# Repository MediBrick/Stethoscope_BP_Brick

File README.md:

# Stethoscope with Pressure Sensor

The stethoscope and blood pressure brick consists of a sound as well as pressure recorder. For sound the I2S (Inter-Integrated Circuit Sound) bus is used to communicate with the microcontroller. This interface allows streaming and recording audio to an audio codec board. The Everest Semiconductor [ES8388 audio codec](datasheets/ES8388%20DS.pdf) was chosen because its supported by Arduino Audio Tools library and Arduino Audio Driver and because Espressif created the Lyrat Audio modules with published reference [designs](datasheets/esp32-lyrat-v4-schematic.pdf).

Sound was recorded with pui audio analog MEMS microphones [AMM-2742](datasheets/Microphone-AMM-2742-T-R.pdf) that are mounted on the printed circuit board.

However a new design is developed to use electret microphones that are attached to the flexible stethoscope tubing.

Two microphones are used where one is connected to the stethoscope and the other recording the background. An [dual differential amplifier](datasheets/opa344.pdf) is used to low pass filter and amplify the signal from the microphone, however amplification would not be needed for the ES8388 codec. Pressure is measured with a Honeywell MPR pressure sensor [MPRLS0300YG](datasheets/MPR_Pressure_HWSC_S_A0016036563_1-3073392.pdf) that convers the physiological range of 0 to 200 mm Hg.

## Costs &#36;

| Item        | Quantity at Purchase | Costs  | Source            | Cost per Brick
|---                          | ---  | ---    | ---               | ---
| Microcontroller             |  1   | $17.5  | [Adafruit](https://www.adafruit.com/product/5477)          | $17.5
| Display                     |  5   | $13    | [Amazon](https://a.co/d/1QH0Ab9)            | $3
| Button                      | 25   | $9     | [Amazon](https://a.co/d/8KAuTwC) | $0.5 
| Battery                     |  1   | $10     | [Adafruit](https://www.adafruit.com/product/258)        | $10
| PCB                         |  5   | $45.18 | PCBWay            | $9
| Parts and Assembly          |  2   | $56.55 | PCBWay            | $29
| MPRLS0300YG (pressure)      |  2   | $35    | [DigiKey](https://www.digikey.com/en/products/detail/honeywell-sensing-and-productivity-solutions/MPRLS0300YG00001B/10231660) | $17.5
| PUI AOM-5024L-HD-R (microphone)  |  2  | $4.2 | [Mouser](https://mou.sr/43AdqZY) | $8.4
| 3.5mm Audio jack stereo out(*)   | 1 | $0.9 | [Mouser](https://mou.sr/4uOWvy2) | $0.9
| 3.5mm Audio jacl mic in & stereo out(*) | 1 | $1.2 | [Mouser](https://mou.sr/4fyV8PS) | $1.2 |
| Stethoscope                 |  1   | $25    | [Amazon](https://a.co/d/7tQgoKs) | $25
| Arm Cuff                    |  1   | $17    | [Amazon](https://a.co/d/gKueGYV) | $17
| Assorted Wires              |8m    | $15    | [Amazon](https://a.co/d/58djefc) | $1
| Assorted Screws and Nuts    |100   |  $7    | Amazon            | $0.05
| Silocone Tubing             |  1   |  $9    | [Amazon](https://a.co/d/5GLJtFr) | $2
| Luer Lock female 3/32 barb  | 10   |  $9    | [Amazon](https://a.co/d/hxruOyw) | $1
| Luer Lock male 5/32 barb    | 10   |  $8    | [Amazon](https://a.co/d/c4cmtBQ) | $1
| Stainless Steel Tubing      |250mm | $10    | Amazon            | $2 |
| Assorted 3D printed parts   |      |        |                   | $3
|  **(*)** if not available at manufacturer, DIY |
| **Total with blood pressure**     |      |        |                   | **$140**
| **Total without blood pressure**  |      |        |                   | **$100**

Electronic components, excluding the pressure sensor, are $14 per board.

The pressure sensor was mounted in-house as the PCB assembly service did not have access to an inexpensive source.

## Software &#128187;

Main Program in Arduino folder:

- MediBrick_Stethoscope_BP_Microcontroller_Software: Refer to [Microcontroller_Software.md](Microcontroller_Software.md) for installation and usage instructions.

Test software is located in Arduino folder.

- MediBrick_Stethoscope_ES8388_to_CSV:
Prints the two-channel audio signal to the serial port for visualization with SerialUI application.

- MediBrick_Stethoscope_ES8388_TestSound: Creates test tone in left and right channels for headphones.

- MediBrick_Stethoscope_ES8388_to_Headphone: Plays the recorded sound to the headphone.

- MediBrick_Stethoscope_PressureTest: Test the arm cuff pressure sensor.

## Electronics Design &#128268;

The following files are needed for PCB manufacturing and assembly at PCBWay.

- [Bill of Materials](KiCad/pcbway_production/2026-06-14-11-51-50/Sound.kicad_pcb_bom.csv)
- [Gerber Manufacturing Files](KiCad/pcbway_production/2026-06-14-11-51-50/Sound.kicad_pcb_gerber.zip)
- [Component Placement](KiCad/pcbway_production/2026-06-14-11-51-50/Sound.kicad_pcb_positions.csv)

The current design source is in [`KiCad`](KiCad/). The previous Eagle design is retained in [`Eagle`](Eagle/).

## 3D Printed Parts &#9881;
These are the links to the OnShape Design files, which you can edit and modify if you have an OnShape account (OnShape has free academic accounts).

- Microphone Housing
  - [Stethoscope Microphone Bottom](https://cad.onshape.com/documents/f23280f0a46d3d6c755669df/w/b75e085438cd92ba1b26b647/e/00c40c7437b1518e003bac9d)
  - [Stethoscope Microphone Top](https://cad.onshape.com/documents/ef2b037c38f1baa1c0b23c04/w/556b341c46d5852ab7c96559/e/758f32969c2d9c1e8976b746)

- MediBrick Casing (print each part separately) [This is not yet updated for new microphone]
  - [Brick Top/Board](https://cad.onshape.com/documents/ebcdcbc3e7eb802e05aa7127/w/92c7f2c4a3604ac0392e9e89/e/23d2cedb30284d3e07ce3fd7)
  - [Brick Bottom / Microcontroller](https://cad.onshape.com/documents/3fee40e68f3fb61ffdb812bb/w/65bb78ada38672d141a5d154/e/0ff82183503e2fd6c450e151)
  - [Stethoscope Interface Plate ](https://cad.onshape.com/documents/06546d5c2b6ecb0931149c5d/w/2aa54258cb58c3e795c7fea9/e/823e2851771a01788a8faacf)

## PCB Manufacturing Instructions &#128736;
When ordering at PCBWay:

Standard PCB
- Single pieces
- 70 x 70 mm
- 2 layers
- FR-4, TG 150-160
- Thickness 1.6 mm
- Minimum track width and spacing 0.15 mm
- Minimum through-hole diameter 0.25 mm
- No edge connectors
- Surface finish ENIG, 1U"
- Via process: Tenting Vias
- 1 oz Cu

Assembly Service
- Turnkey
- Single pieces
- Top side

Other Parameters
- Use the current BOM and component-placement files linked above for part counts
- Number of BGA/QFN parts: 1
- Through-hole connectors are installed separately

Customized Services and Advanced Options
- Leave as is

## Assembly Instructions &#128736;
  - [Assembly Instructions](./Assembly.md) 
 
## Audio Filters

The firmware provides adjustable high-pass and low-pass filters, software gain, and two-channel noise cancellation. These settings can be changed through the serial command interface described in [Microcontroller_Software.md](Microcontroller_Software.md).

The older offline filter-analysis utility remains available in [Compute_Filter_Coefficients.py](Compute_Filter_Coefficients.py).

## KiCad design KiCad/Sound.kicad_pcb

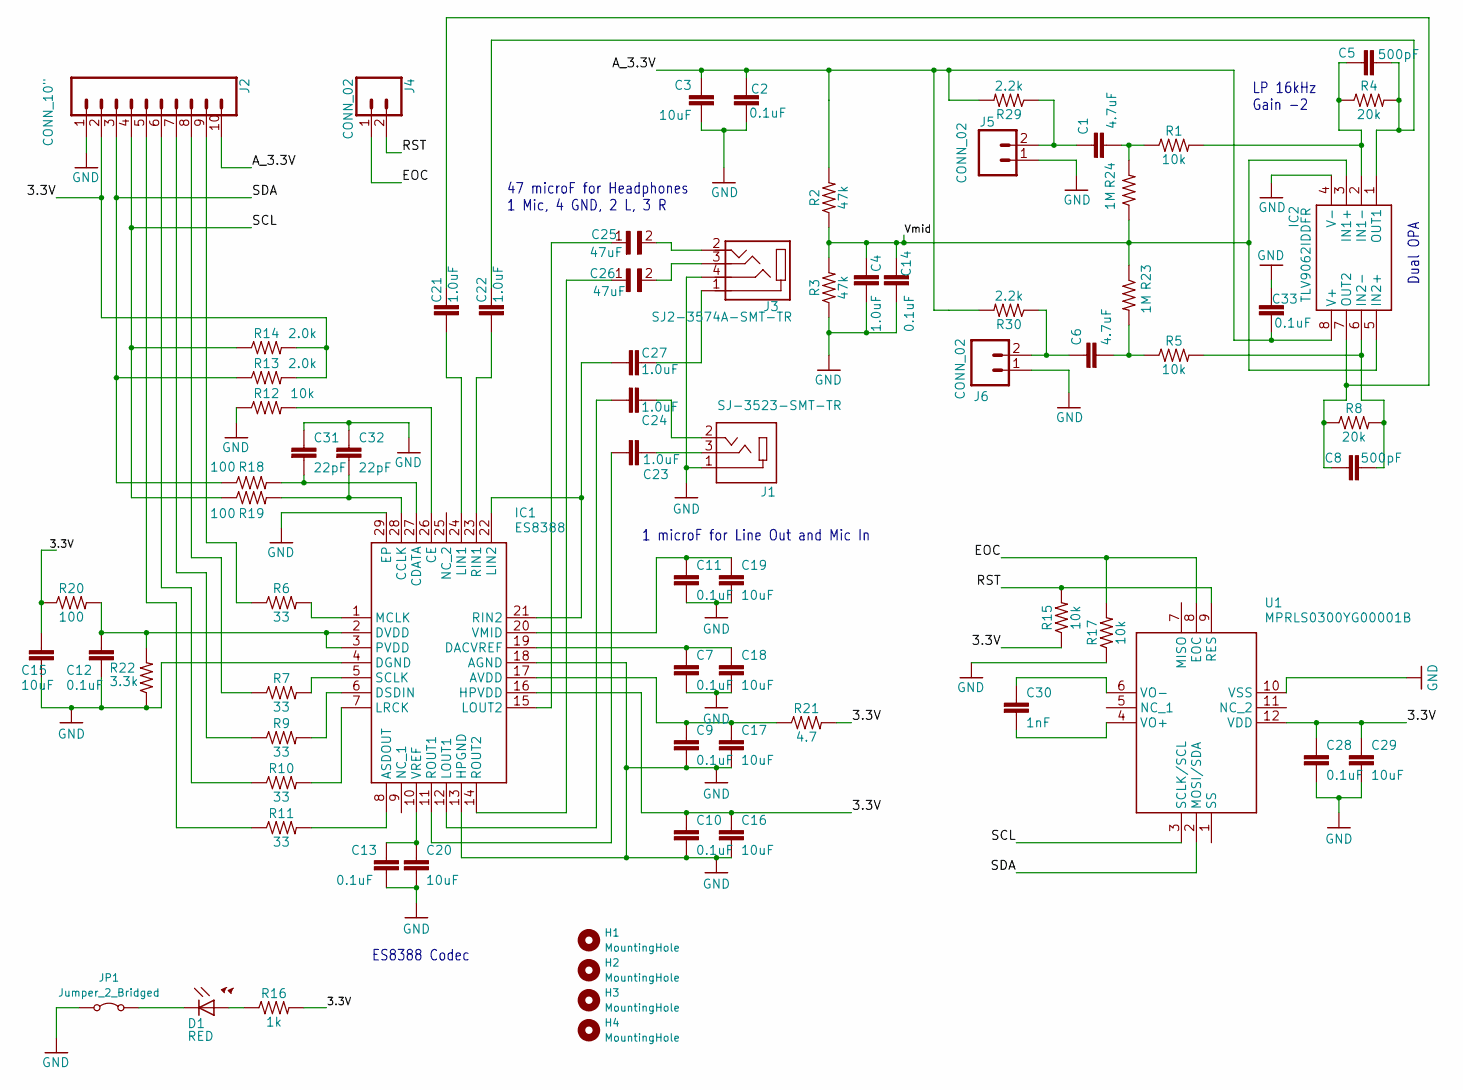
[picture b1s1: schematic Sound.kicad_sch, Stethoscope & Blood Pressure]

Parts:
C1, C6: 4.7uF; 0603
C2, C7, C9, C10, C11, C12, C13, C14, C28, C33: 0.1uF; 0603
C3, C15, C16, C17, C18, C19, C20, C29: 10uF; 0603
C4, C21, C22, C23, C24, C27: 1.0uF; 0603
C5, C8: 500pF; 0603
C25, C26: 47uF; CAPC1608X100N
C30: 1nF; 0603
C31, C32: 22pF; 0603
D1: RED; LED-0603
H1, H2, H3, H4: MountingHole; MountingHole_3.2mm_M3
IC1: ES8388; QFN45P400X400X80-29N
IC2: TLV9062IDDFR; SOT_62IDDFR_TEX-L
J1: SJ-3523-SMT-TR; CUI_SJ-3523-SMT-TR
J2: CONN_10"; 1X10
J3: SJ2-3574A-SMT-TR; CUI_SJ2-3574A-SMT-TR
J4, J5, J6: CONN_02; 1X02
JP1: Jumper_2_Bridged; Jumper_2_NC_Trace_NoSilk
R1, R5, R12, R15, R17: 10k; 0603
R2, R3: 47k; 0603
R4, R8: 20k; 0603
R6, R7, R9, R10, R11: 33; 0603
R13, R14: 2.0k; 0603
R16: 1k; 0603
R18, R19, R20: 100; 0603
R21: 4.7; 0603
R22: 3.3k; 0603
R23, R24: 1M; 0603
R29, R30: 2.2k; 0603
U1: MPRLS0300YG00001B; MPRLS0300YG00001B_HNW

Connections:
/3.3V: C10.1, C15.1, C16.1, C28.1, C29.1, IC1.16 (HPVDD), J2.2, R13.2, R14.2, R15.1, R16.2, R20.1, R21.2, U1.12 (VDD)
/A_3.3V: C2.1, C3.1, C33.2, IC2.8 (V+), J2.10, R2.2, R29.2, R30.2
/EOC: J4.1, R17.2, U1.8 (EOC)
/RST: J4.2, R15.2, U1.9 (RES)
/SCL: J2.4, R14.1, R19.1, U1.3 (SCLK/SCL)
/SDA: J2.3, R13.1, R18.1, U1.2 (MOSI/SDA)
/Vmid: C4.1, C14.1, IC2.3 (IN1+), IC2.5 (IN2+), R2.1, R3.2, R23.1, R24.1
GND: C2.2, C3.2, C4.2, C7.2, C9.2, C10.2, C11.2, C12.2, C13.2, C14.2, C15.2, C16.2, C17.2, C18.2, C19.2, C20.2, C28.2, C29.2, C31.1, C32.1, C33.1, IC1.4 (DGND), IC1.13 (HPGND), IC1.18 (AGND), IC1.29 (EP), IC2.4 (V-), J1.1, J2.1, J3.4, J5.1, J6.1, JP1.1 (A), R3.1, R12.1, R17.1, R22.1, U1.10 (VSS)
unnamed: C1.1, J5.2, R29.1
unnamed: C1.2, R1.1, R24.2
unnamed: C6.1, J6.2, R30.1
unnamed: C6.2, R5.1, R23.2
unnamed: C23.1, J1.3
unnamed: C24.1, J1.2
unnamed: C25.2, J3.2
unnamed: C26.2, J3.3
unnamed: C27.2, J3.1
unnamed: D1.A, R16.1
unnamed: IC1.8 (ASDOUT), R11.2
unnamed: C9.1, C17.1, IC1.17 (AVDD), R21.1
unnamed: C32.2, IC1.28 (CCLK), R19.2
unnamed: C31.2, IC1.27 (CDATA), R18.2
unnamed: IC1.26 (CE), R12.2
unnamed: C7.1, C18.1, IC1.19 (DACVREF)
unnamed: IC1.6 (DSDIN), R9.2
unnamed: C12.1, IC1.2 (DVDD), IC1.3 (PVDD), R20.2, R22.2
unnamed: C21.1, IC1.24 (LIN1)
unnamed: C27.1, IC1.21 (RIN2), IC1.22 (LIN2)
unnamed: C24.2, IC1.12 (LOUT1)
unnamed: C25.1, IC1.15 (LOUT2)
unnamed: IC1.7 (LRCK), R10.2
unnamed: IC1.1 (MCLK), R6.2
unnamed: C22.1, IC1.23 (RIN1)
unnamed: C23.2, IC1.11 (ROUT1)
unnamed: C26.1, IC1.14 (ROUT2)
unnamed: IC1.5 (SCLK), R7.2
unnamed: C11.1, C19.1, IC1.20 (VMID)
unnamed: C13.1, C20.1, IC1.10 (VREF)
unnamed: C5.1, IC2.2 (IN1-), R1.2, R4.1
unnamed: C8.2, IC2.6 (IN2-), R5.2, R8.2
unnamed: C5.2, C22.2, IC2.1 (OUT1), R4.2
unnamed: C8.1, C21.2, IC2.7 (OUT2), R8.1
unnamed: J2.5, R11.1
unnamed: J2.6, R10.1
unnamed: J2.7, R9.1
unnamed: J2.8, R7.1
unnamed: J2.9, R6.1
unnamed: D1.C, JP1.2 (B)
unnamed: C30.2, U1.4 (VO+)
unnamed: C30.1, U1.6 (VO-)

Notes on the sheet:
ES8388 Codec
1 microF for Line Out and Mic In
LP 16kHz Gain -2
Dual OPA
47 microF for Headphones 1 Mic, 4 GND, 2 L, 3 R

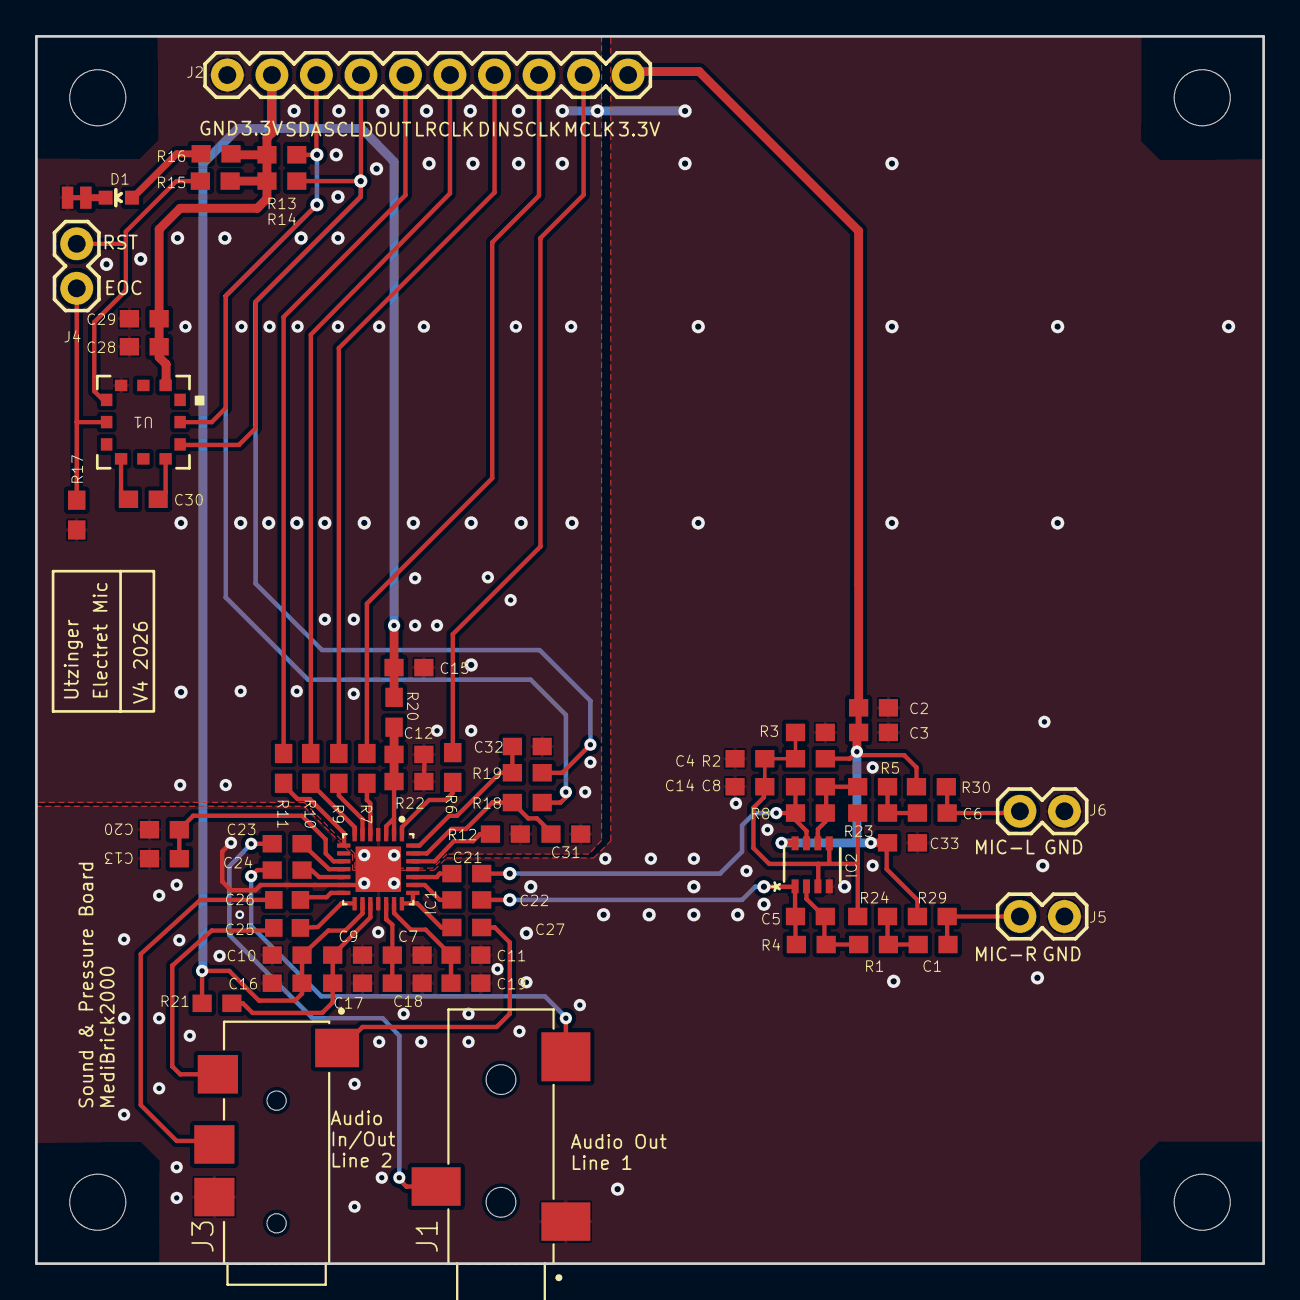
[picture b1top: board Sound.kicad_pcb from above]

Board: 2 copper layers, 70.0 x 70.0 mm, 74 parts (0 on the bottom side), 50 nets.

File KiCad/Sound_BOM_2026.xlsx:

Item # | *Designator | *Qty | Manufacturer | *Mfg Part # | Description / Value | Vendor Part # | *Package/Footprint | Mounting Type | Your Instructions / Notes | *Unit Price(2 sets) | *Total | *Delivery Time | *Actual Purchase Mfg Part # | Customer Reply
1 | C2, C7, C9, C10, C11, C12, C13, C14, C28, C33 | 10 | muRata | GRM188R71H104KA93D | 100nF | C77055 | 0603 | SMD |  |  | 0
2 | C4, C21, C22, C23, C24, C27 | 6 | muRata | GCM188R71E105KA64D | 1.0uF | C85862 | 0603 | SMD |  |  | 0
3 | C3, C15, C16, C17, C18, C19, C20, C29 | 8 | muRata | GRM188R61A106KE69D | 10uF | C77044 | 0603 | SMD |  |  | 0
4 | C1, C6 | 2 | muRata | GRM188R61E475KE11D | 4.7uF | C90057 | 0603 | SMD |  |  | 0
5 | C5, C8 | 2 | YAEGO | CC0603JRNPO9BN501 | 500pF | C3879676 | 0603 | SMD |  |  | 0
6 | C25, C26 | 2 | muRata | GRM188R60J476ME15D | 47uF | C140782 | 0603 | SMD |  |  | 0
7 | C30 | 1 | muRata | GRM1885C1H102JA01D | 1nF | C77026 | 0603 | SMD |  |  | 0
8 | C31, C32 | 2 | muRata | GCG1885G1H220JA01D | 22pF | C3884601 | 0603 | SMD |  |  | 0
9 | R1, R5, R12, R15, R17 | 5 | YAGEO | RT0603BRD0710KL | 10k | C95204 | 0603 | SMD |  |  | 0
10 | R2, R3 | 2 | YAGEO | RC0603JR-0747KL | 47k | C127447 | 0603 | SMD |  |  | 0
11 | R4, R8 | 2 | YAGEO | RT0603BRD0720KL | 20k | C723637 | 0603 | SMD |  |  | 0
12 | R6, R7, R9, R10, R11 | 5 | YAGEO | RC0603JR-0733RL | 33 | C108407 | 0603 | SMD |  |  | 0
13 | R13, R14 | 2 | YAGEO | RT0603BRB072KL | 2k | C326555 | 0603 | SMD |  |  | 0 |  | RC0603FR-072KL
14 | R16 | 1 | YAGEO | RT0603BRD071KL | 1k | C110776 | 0603 | SMD |  |  | 0
15 | R18, R19, R20 | 3 | YAGEO | RT0603BRD07100RL | 100 | C122970 | 0603 | SMD |  |  | 0
16 | R21 | 1 | YAGEO | RT0603DRE074R7L | 4.7 | C863140 | 0603 | SMD |  |  | 0
17 | R22 | 1 | YAGEO | RT0603BRB073K3L | 3.3k | C860369 | 0603 | SMD |  |  | 0
18 | R23, R24 | 2 | YAGEO | RC0603FR-071ML | 1M | C105578 | 0603 | SMD
19 | R29, R30 | 2 | YAGEO | AC0603FR-072K2L | 2.2k | C125931 | 0603 | SMD
20 | IC1 | 1 | Everest-semi(Everest Semiconductor) | ES8388 | ES8388 | C365736 | QFN-28-EP(4x4) | SMD |  |  | 0
21 | D1 | 1 | XINGLIGHT | XL-1608UBC-04 | Blue LED | C965807 | 0603 | SMD |  |  | 0
22 | J1 | 1 | CUI Devices | SJ-3523-SMT-TR | SJ-3523-SMT-TR, 3.5mm Audio Jack | C4991872 | Custom | SMD | https://mou.sr/4uOWvy2 |  | 0
23 | J2 | 1 |  | Connector | 1x10 | Do not populate
24 | J3 | 1 | CUI Devices | SJ2-3574A-SMT-TR | SJ2-3574A-SMT-TR, 3.5mm Audio Jack with microphone | C4991637 | Custom | SMD | https://mou.sr/4fyV8PS |  | 0 | 7-10 Workdays
25 | J4, J5, J6 | 3 |  | Connector | 1x2 | Do not populate
26 | JP1 | 1 |  | Jumper NC |  | Do not populate
27 | IC2 | 1 | Texas Instruments | TLV9062IDDFR | 10 MHz, RRIO, CMOS operational amplifier | C2867884 | TSOT-23-8 | SMD |  |  | 0 | 7-10 Workdays
 |  |  |  |  |  |  |  |  |  | Component Cost | 0
 |  | 69

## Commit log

2025-12-08 Release
2025-12-09 Documentation
2026-04-28 Update README.md
    Add link for pressure sensor from DigiKey.
2026-04-28 Update assembly.md: hot air soldering
    Added instructions for hot-air pressure sensor soldering.
2026-04-28 Update assembly.md
    Updated electronic assembly section.
2026-04-28 Add complete microcontroller software
2026-04-28 Add link for pressure sensor.
2026-04-28 Typos
2026-04-28 Update assembly.md
    Cleared up 3D printing wording.
2026-04-28 Microcontroller Software for Stethoscope/BP MediBrick
2026-04-28 Update README.md: Add microcontroller software section
2026-04-28 Update README.md: typos
2026-04-29 Update README.md: Microphone Assembly
2026-04-30 Microcontroller Software
2026-04-30 Update README.md: MC Software section
2026-05-07 Update assembly.md for ALL instructions
2026-06-11 Remove vendored libraries and update docs for external dependencies
2026-06-11 Add changelog entry for 2026-06-10 release
2026-06-14 Add KiCad PCB design and enhance firmware
